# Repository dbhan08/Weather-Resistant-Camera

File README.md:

# Weather-Resistant Camera

An STM32-based enclosure that keeps a camera lens usable in rain and frost.
A vision model on the host PC (or, with the TFLite Micro path, on the MCU)
detects water on the lens and triggers a servo wiper; an on-die thermistor
turns a heating pad on below a threshold.  UIUC ECE 445 senior design,
Spring 2025.

## Run it

```bash
# firmware: open Final.ioc in STM32CubeIDE, build main.c, flash the Nucleo-F4
# vision (original OpenCV heuristic):
python final_code.py               # webcam -> HSV mask -> % coverage -> "START" over serial
# vision (CNN, see CNN/README.md):
python -m lens_soiling.infer runs/procedural/soilnet.pt --camera 1 --port COM3
```

## How it works

- **Firmware (`main.c`).**  TIM2 PWM drives the servo; `Set_Servo_Angle`
  maps 0–180° to a 210–1050 tick pulse.  ADC1 reads the internal temperature
  sensor with the factory `TS_CAL1/2` calibration, and drives a MOSFET on PA5
  to switch the heater.  USART2 at 115200 baud accepts 5-byte commands
  (`START`, `STOPP`) from the PC; `START` sweeps the wiper 60→115→60°.
- **Vision, heuristic (`final_code.py`).**  HSV threshold on low saturation
  and high value, morphological close, contours, enclosing circles, then
  percent of masked pixels.  Over 5 % sends `START`.
- **Vision, CNN (`CNN/`).**  Tile-level classifier: a ported pretrained
  raindrop CNN distilled into a ~20 k-parameter int8 model for TFLite Micro,
  plus a tested PyTorch fallback trained on synthetic drops and frost.
- **Hardware.**  KiCad PCB (`PCB Design*/`), 5 V and 3.3 V regulators, MOSFET
  heater switch, logic-level shifter, servo header.  Demo ran on the Nucleo
  dev board after the second PCB's MCU was damaged during hand soldering.

## Layout

```
main.c, Final.ioc          STM32 firmware and CubeMX project
final_code.py              OpenCV heuristic + serial trigger (PC)
python_to_stm_comm.py      serial protocol smoke test
CNN/                       CNN detection: pretrained port + from-scratch pipeline
Servo Motor code/, Temperature sensor code/   subsystem test firmware
PCB Design*/               KiCad
Lab Notebooks/             per-member design logs
```

## Stack

C (STM32 HAL), Python, OpenCV, PyTorch, TensorFlow Lite Micro, KiCad.

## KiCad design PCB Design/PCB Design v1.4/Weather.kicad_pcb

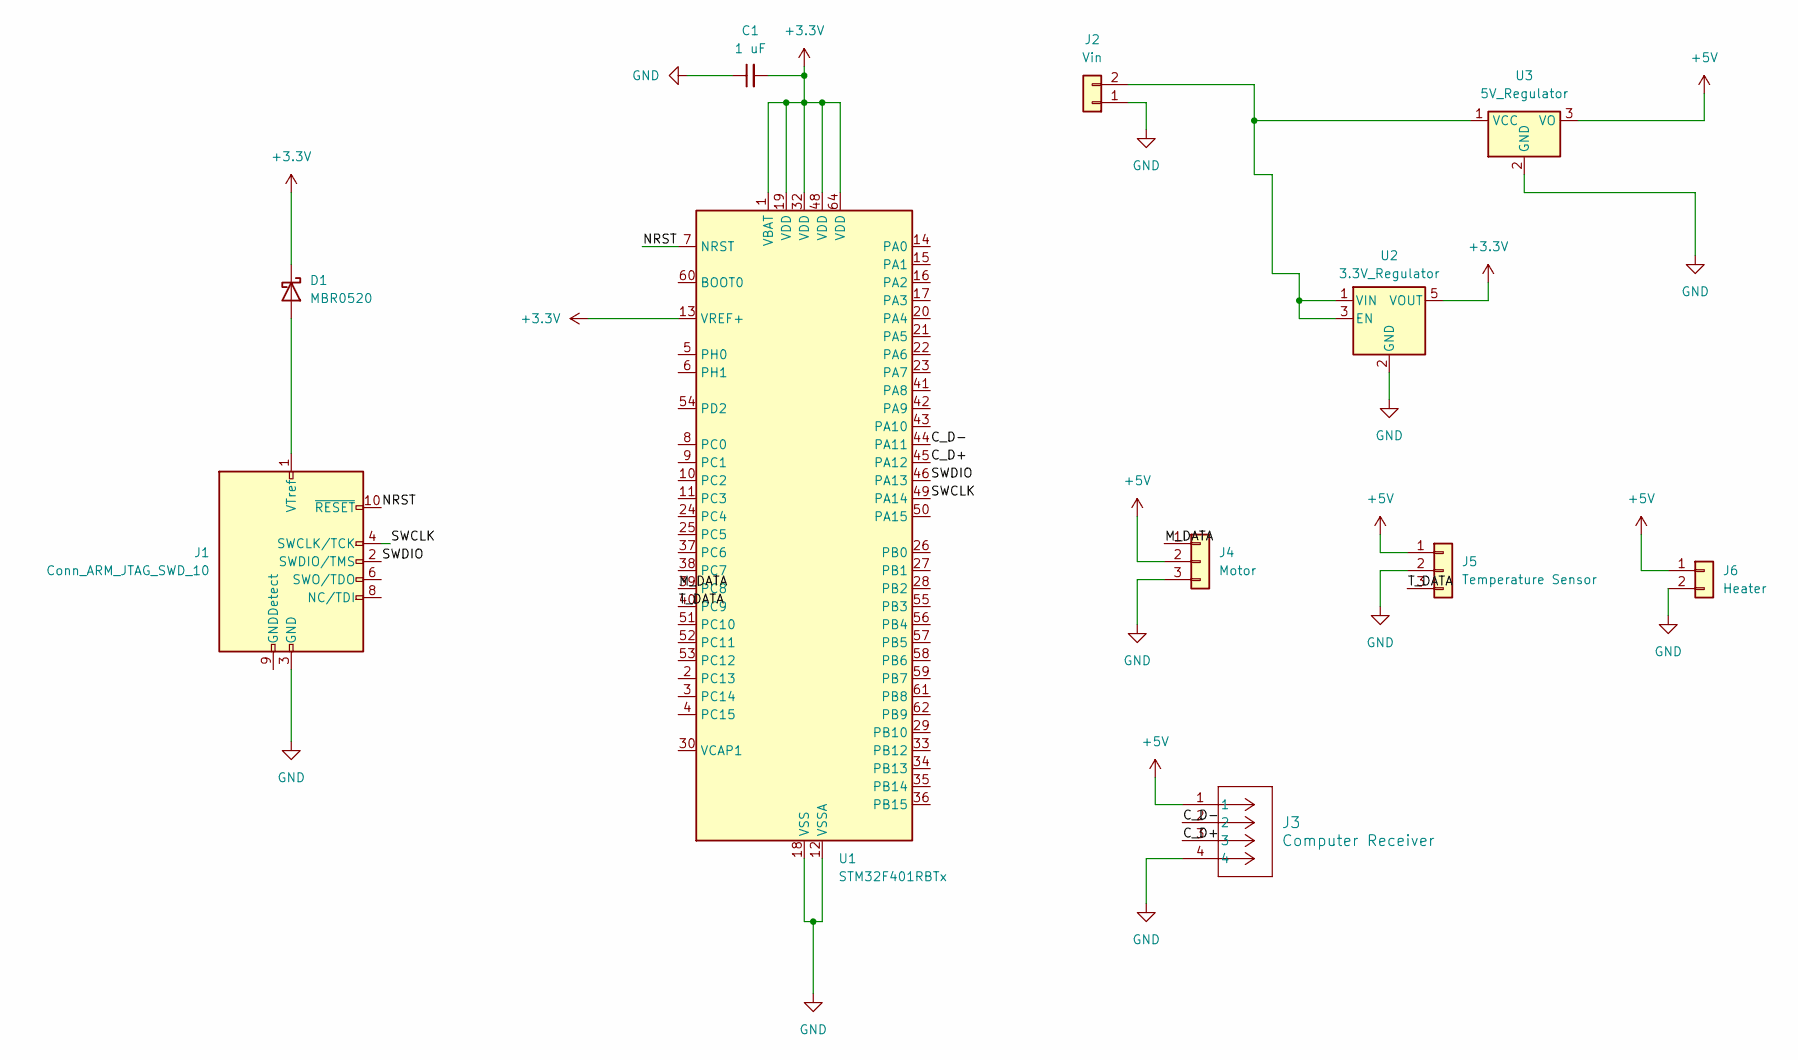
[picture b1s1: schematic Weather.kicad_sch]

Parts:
C1: 1 uF; C_0805_2012Metric_Pad1.18x1.45mm_HandSolder
D1: MBR0520; D_SOD-123
J1: Conn_ARM_JTAG_SWD_10; PinHeader_2x05_P1.27mm_Vertical
J2: Vin; Molex_KK-254_AE-6410-02A_1x02_P2.54mm_Vertical
J3: Computer Receiver; CONN_USB-AP-S-RA-SMT_ADM
J4: Motor; Molex_KK-254_AE-6410-03A_1x03_P2.54mm_Vertical
J5: Temperature Sensor; Molex_KK-254_AE-6410-03A_1x03_P2.54mm_Vertical
J6: Heater; Molex_KK-254_AE-6410-02A_1x02_P2.54mm_Vertical
U1: STM32F401RBTx; LQFP-64_10x10mm_P0.5mm
U2: 3.3V_Regulator; SOT-23-5_HandSoldering
U3: 5V_Regulator; TO-252-2

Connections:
+3.3V: C1.2, D1.1 (K), U1.1 (VBAT), U1.13 (VREF+), U1.19 (VDD), U1.32 (VDD), U1.48 (VDD), U1.64 (VDD), U2.5 (VOUT)
+5V: J3.1, J4.2, J5.1, J6.1, U3.3 (VO)
/C_D+: J3.3, U1.45 (PA12)
/C_D-: J3.2, U1.44 (PA11)
/M_DATA: J4.1, U1.39 (PC8)
/NRST: J1.10 (~RESET), U1.7 (NRST)
/SWCLK: J1.4 (SWCLK/TCK), U1.49 (PA14)
/SWDIO: J1.2 (SWDIO/TMS), U1.46 (PA13)
/T_DATA: J5.3, U1.40 (PC9)
GND: C1.1, J1.3 (GND), J1.5 (GND), J2.1, J3.4, J4.3, J5.2, J6.2, U1.12 (VSSA), U1.18 (VSS), U1.31 (VSS), U1.47 (VSS), U1.63 (VSS), U2.2 (GND), U3.2 (GND)
unnamed: D1.2 (A), J1.1 (VTref)
unnamed: J2.2, U2.1 (VIN), U2.3 (EN), U3.1 (VCC)

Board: 2 copper layers, 11 parts (0 on the bottom side), 12 nets, no tracks yet.

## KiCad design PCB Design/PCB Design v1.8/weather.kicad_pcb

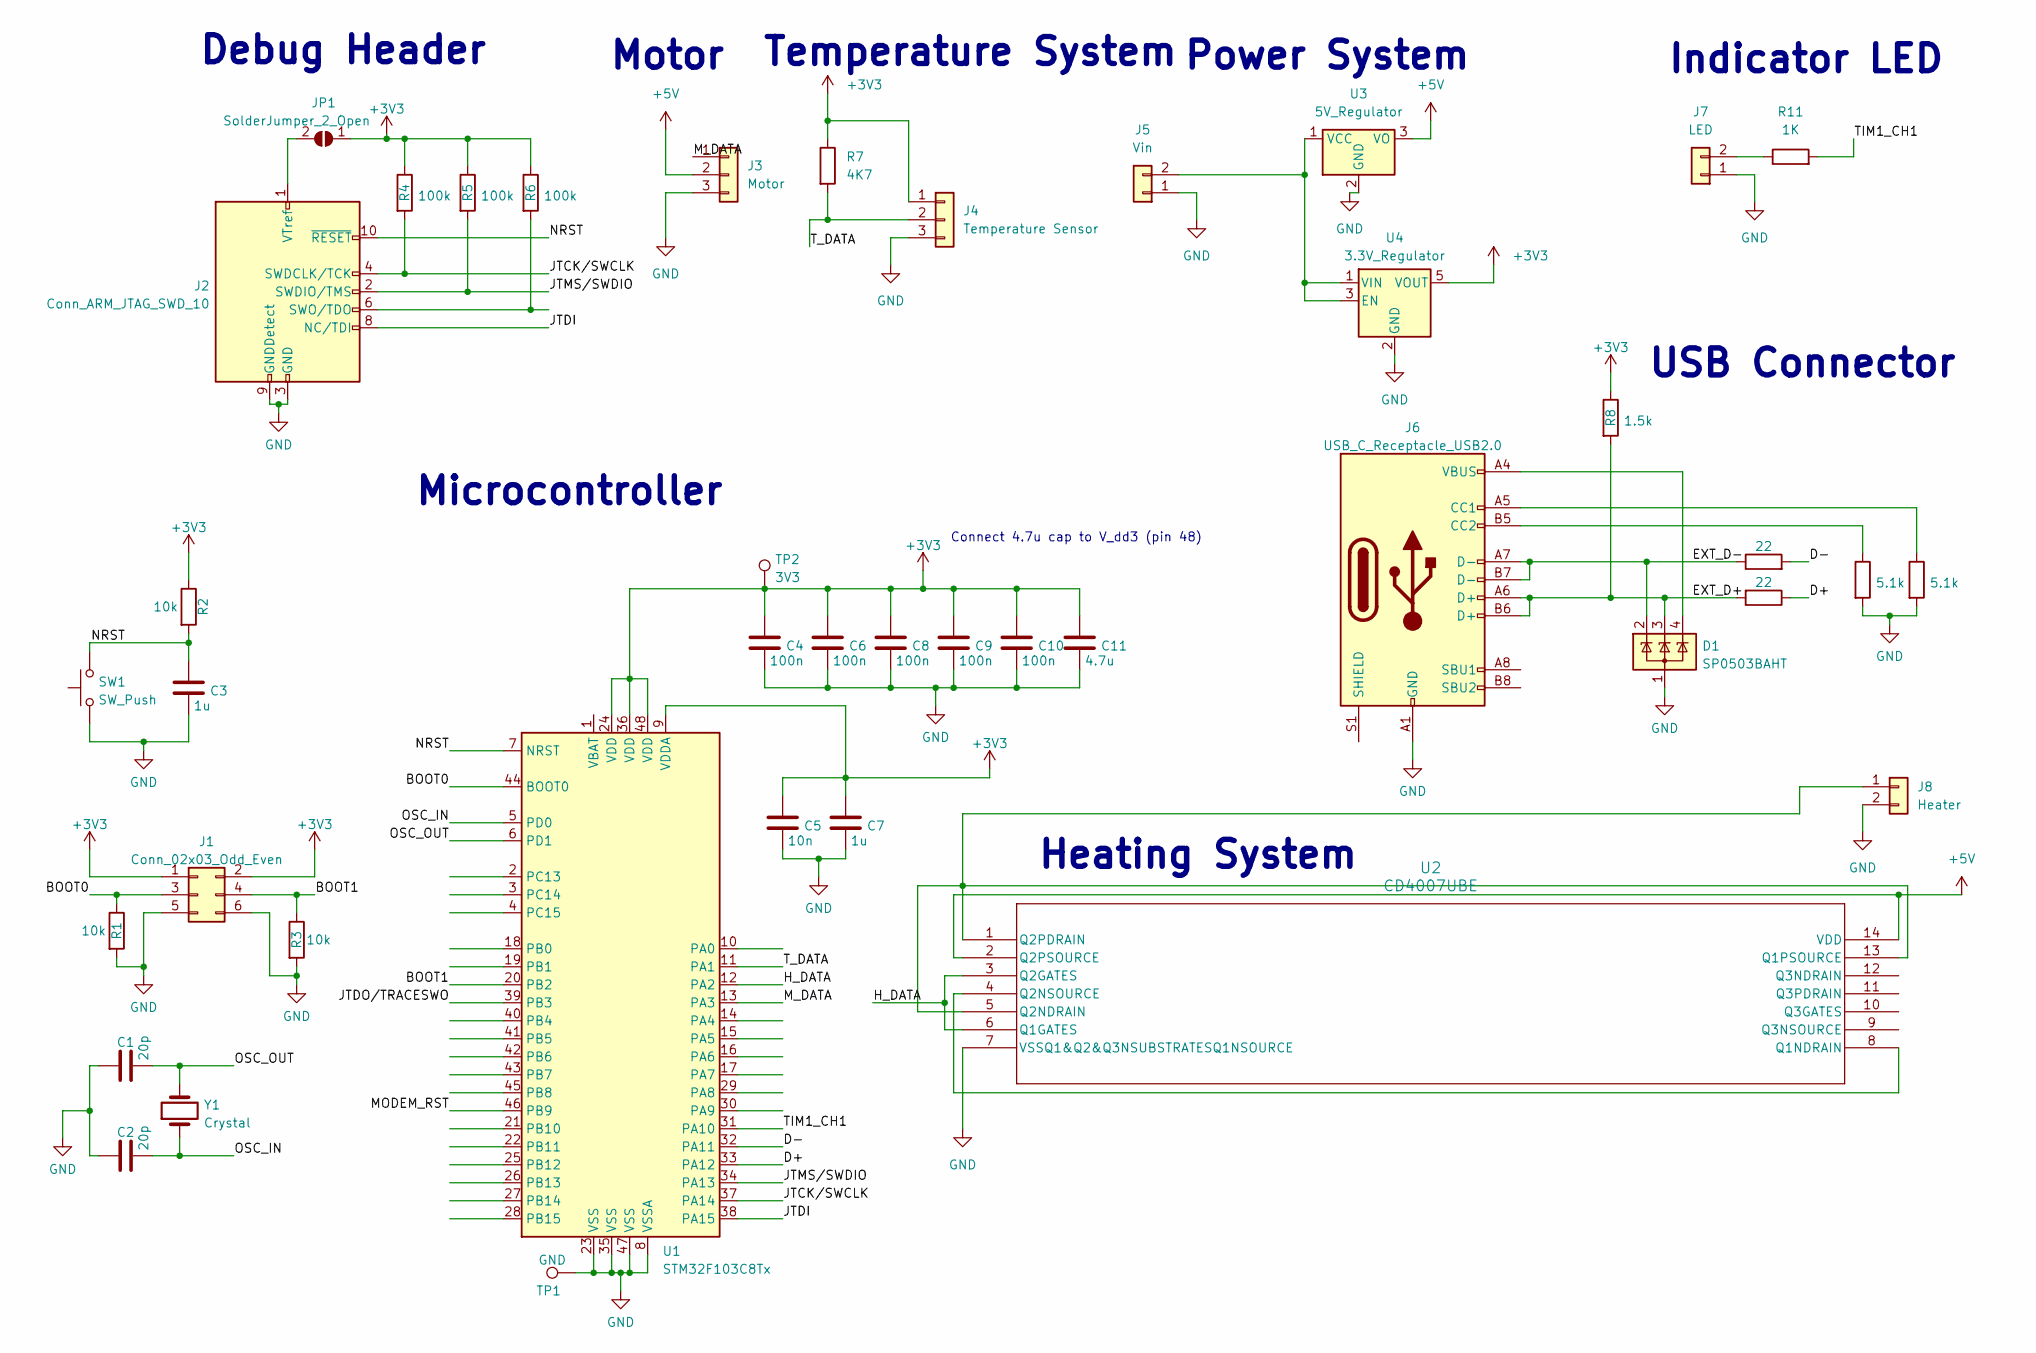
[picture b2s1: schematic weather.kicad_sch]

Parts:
C1, C2: 20p; C_0603_1608Metric
C3, C7: 1u; C_0603_1608Metric
C4, C6, C8, C9, C10: 100n; C_0603_1608Metric
C5: 10n; C_0603_1608Metric
C11: 4.7u; C_0603_1608Metric
D1: SP0503BAHT; SOT-143
J1: Conn_02x03_Odd_Even; PinSocket_2x03_P2.54mm_Vertical
J2: Conn_ARM_JTAG_SWD_10; IDC-Header_2x05_P2.54mm_Vertical
J3: Motor; Molex_KK-254_AE-6410-03A_1x03_P2.54mm_Vertical
J4: Temperature Sensor; Molex_KK-254_AE-6410-03A_1x03_P2.54mm_Vertical
J5: Vin; Molex_KK-254_AE-6410-02A_1x02_P2.54mm_Vertical
J6: USB_C_Receptacle_USB2.0; USB_C_Receptacle_Amphenol_12401610E4-2A_CircularHoles
J7: LED; Molex_KK-254_AE-6410-02A_1x02_P2.54mm_Vertical
J8: Heater; Molex_KK-254_AE-6410-02A_1x02_P2.54mm_Vertical
JP1: SolderJumper_2_Open; SolderJumper-2_P1.3mm_Open_TrianglePad1.0x1.5mm
R1, R2, R3: 10k; R_0603_1608Metric
R4, R5, R6: 100k; R_0603_1608Metric
R7: 4K7; R_0603_1608Metric
R8: 1.5k; R_0603_1608Metric
R9, R10: 22; R_0603_1608Metric
R11: 1K; R_0603_1608Metric
R12, R13: 5.1k; R_0603_1608Metric
SW1: SW_Push; SW_SPST_B3S-1000
TP1: GND; TestPoint_Keystone_5000-5004_Miniature
TP2: 3V3; TestPoint_Keystone_5000-5004_Miniature
U1: STM32F103C8Tx; LQFP-48_7x7mm_P0.5mm
U2: CD4007UBE; N14
U3: 5V_Regulator; TO-252-2
U4: 3.3V_Regulator; SOT-23-5_HandSoldering
Y1: Crystal; Crystal_HC49-U_Vertical

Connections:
+3V3: C4.1, C5.1, C6.1, C7.1, C8.1, C9.1, C10.1, C11.1, J1.1, J1.2, J4.1, JP1.1 (A), R2.1, R4.1, R5.1, R6.1, R7.1, R8.1, TP2.1, U1.9 (VDDA), U1.24 (VDD), U1.36 (VDD), U1.48 (VDD), U4.5 (VOUT)
+5V: J3.2, U2.2 (Q2PSOURCE), U2.14 (VDD), U3.3 (VO)
/BOOT0: J1.3, R1.1, U1.44 (BOOT0)
/BOOT1: J1.4, R3.1, U1.20 (PB2)
/D+: R10.1, U1.33 (PA12)
/D-: R9.2, U1.32 (PA11)
/EXT_D+: D1.3 (K), J6.A6 (D+), J6.B6 (D+), R8.2, R10.2
/EXT_D-: D1.2 (K), J6.A7 (D-), J6.B7 (D-), R9.1
/H_DATA: U1.12 (PA2), U2.3 (Q2GATES), U2.6 (Q1GATES)
/JTCK/SWCLK: J2.4 (SWDCLK/TCK), R4.2, U1.37 (PA14)
/JTDI: J2.8 (NC/TDI), U1.38 (PA15)
/JTDO/TRACESWO: U1.39 (PB3)
/JTMS/SWDIO: J2.2 (SWDIO/TMS), R5.2, U1.34 (PA13)
/MODEM_RST: U1.46 (PB9)
/M_DATA: J3.1, U1.13 (PA3)
/NRST: C3.1, J2.10 (~RESET), R2.2, SW1.2, U1.7 (NRST)
/OSC_IN: C2.2, U1.5 (PD0), Y1.1
/OSC_OUT: C1.2, U1.6 (PD1), Y1.2
/TIM1_CH1: R11.2, U1.31 (PA10)
/T_DATA: J4.2, R7.2, U1.11 (PA1)
GND: C1.1, C2.1, C3.2, C4.2, C5.2, C6.2, C7.2, C8.2, C9.2, C10.2, C11.2, D1.1 (A), J1.5, J1.6, J2.3 (GND), J2.5 (GND), J2.9 (GNDDetect), J3.3, J4.3, J5.1, J6.A1 (GND), J6.A12 (GND), J6.B1 (GND), J6.B12 (GND), J7.1, J8.2, R1.2, R3.2, R12.2, R13.2, SW1.1, TP1.1, U1.8 (VSSA), U1.23 (VSS), U1.35 (VSS), U1.47 (VSS), U2.7 (VSSQ1&Q2&Q3NSUBSTRATESQ1NSOURCE), U3.2 (GND), U4.2 (GND); also elsewhere on the board
unnamed: D1.4 (K), J6.A4 (VBUS), J6.A9 (VBUS), J6.B4 (VBUS), J6.B9 (VBUS)
unnamed: J2.6 (SWO/TDO), R6.2
unnamed: J2.1 (VTref), JP1.2 (B)
unnamed: J5.2, U3.1 (VCC), U4.1 (VIN), U4.3 (EN)
unnamed 25: J6.A5 (CC1), R13.1; also elsewhere on the board
unnamed 26: J6.B5 (CC2), R12.1; also elsewhere on the board
unnamed: J7.2, R11.1
unnamed: J8.1, U2.1 (Q2PDRAIN), U2.5 (Q2NDRAIN), U2.13 (Q1PSOURCE)
unnamed: U2.4 (Q2NSOURCE), U2.8 (Q1NDRAIN)

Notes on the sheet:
Debug Header
Motor
Microcontroller
USB Connector
Temperature System
Heating System
Indicator LED
Connect 4.7u cap to V_dd3 (pin 48)
Power System

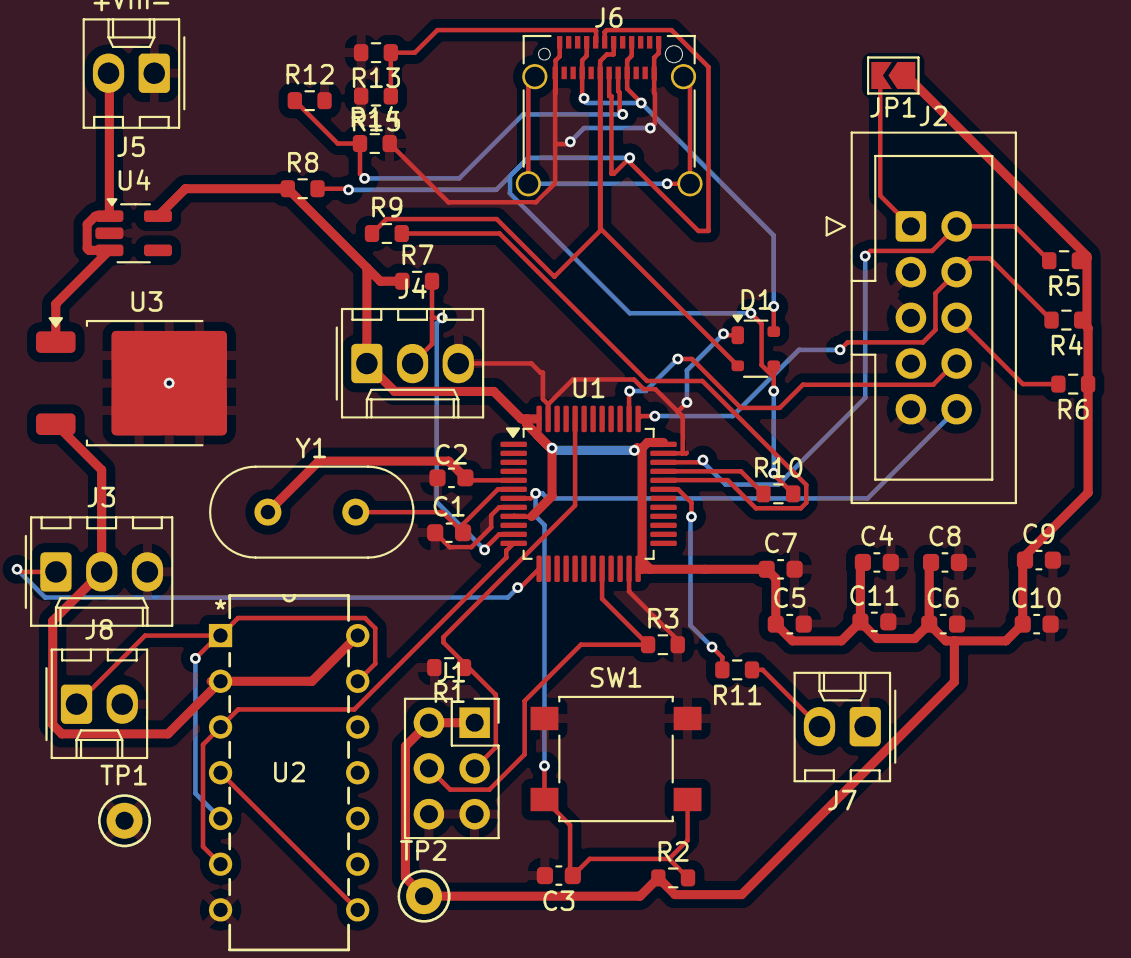
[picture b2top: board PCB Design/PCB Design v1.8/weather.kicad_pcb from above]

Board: 2 copper layers, 44 parts (0 on the bottom side), 28 nets.

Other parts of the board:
R14, R15: 5.1k; R_0603_1608Metric

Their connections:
GND: R14.2, R15.2; also elsewhere on the board
unnamed 25: R15.1; also elsewhere on the board
unnamed 26: R14.1; also elsewhere on the board

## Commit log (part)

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2025-08-11 Adding Project
